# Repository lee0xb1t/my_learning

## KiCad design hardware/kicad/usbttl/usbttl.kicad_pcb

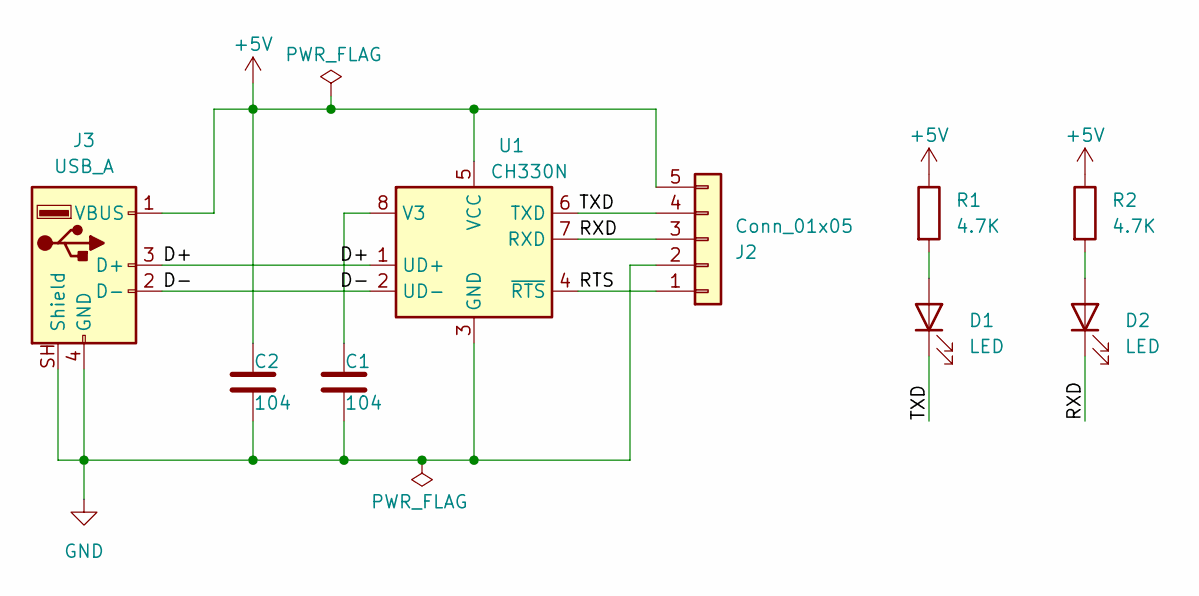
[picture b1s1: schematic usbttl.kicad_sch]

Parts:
C1, C2: 104; C_0603_1608Metric
D1, D2: LED; LED_0603_1608Metric
J2: Conn_01x05; PinHeader_1x05_P2.54mm_Horizontal
J3: USB_A; USB_A_CNCTech_1001-011-01101_Horizontal
R1, R2: 4.7K; R_0603_1608Metric
U1: CH330N; SOIC-8_3.9x4.9mm_P1.27mm

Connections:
+5V: C2.1, J2.5, J3.1 (VBUS), R1.1, R2.1, U1.5 (VCC)
/D+: J3.3 (D+), U1.1 (UD+)
/D-: J3.2 (D-), U1.2 (UD-)
/RTS: J2.1, U1.4 (~RTS)
/RXD: D2.1 (K), J2.3, U1.7 (RXD)
/TXD: D1.1 (K), J2.4, U1.6 (TXD)
GND: C1.2, C2.2, J2.2, J3.4 (GND), J3.SH (Shield), U1.3 (GND)
unnamed: D1.2 (A), R1.2
unnamed: D2.2 (A), R2.2
unnamed: C1.1, U1.8 (V3)

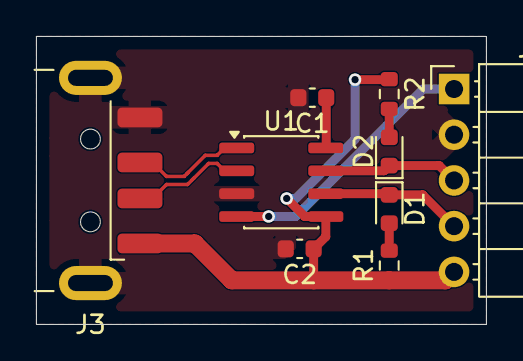
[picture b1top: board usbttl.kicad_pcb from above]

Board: 2 copper layers, 25.0 x 16.0 mm, 9 parts (0 on the bottom side), 10 nets.

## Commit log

2026-03-21 qml and c++ interact
2026-04-05 Learn windows wdf driver
2026-04-06 kdfm associate physical device
2026-04-12 add wdm code
2026-04-12 change name
2026-05-21 kicad
2026-06-20 learn vmp reverse
2026-06-21 Add vmp reverse blog
2026-06-21 add vmp1.63
2026-06-24 vm3.5分析
